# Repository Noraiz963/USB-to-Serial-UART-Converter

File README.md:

# USB to Serial (UART) Converter

A USB Type-C to Serial (UART) converter designed in KiCad, built around the CP2102 USB-to-UART bridge IC — lets you connect a microcontroller's serial pins to a computer's USB port for programming, debugging, or serial communication.

## Why This Exists

Modern PCs only expose USB — there's no native way to talk to a device that "speaks" UART (TX/RX serial). The CP2102 sits in between and acts as a protocol translator: it handles USB enumeration and packetization on one side, and generates real asynchronous serial (UART) signals on the other. Once connected, the PC's OS loads it as a **Virtual COM Port** (e.g. `COM5` on Windows, `/dev/ttyUSB0` on Linux), so any serial terminal or IDE (Arduino Serial Monitor, PuTTY, minicom) can talk to the target microcontroller exactly as if it were plugged into a physical RS-232 port.

## Circuit Overview

- **USB Type-C input**: USB-C receptacle (J1) with CC1/CC2 pull-down resistors for proper USB-C power delivery negotiation, plus ESD protection
- **USB-to-UART bridge**: CP2102 (U1) handles the USB-to-serial conversion, exposing TX/RX lines on the output header
- **Status indicator**: LED with current-limiting resistor, indicating activity/power
- **Decoupling**: Capacitors placed across VBUS/VDD to stabilize the CP2102's supply
- **Reset**: RST line broken out to the output header for manual reset control
- **Output header**: 5-pin header exposing RST, TX, RX, VBUS, and GND — standard pinout for connecting to microcontroller boards (e.g. ESP32, STM32, Arduino) for flashing or serial monitoring

## Signal Flow (Concept)

**PC → Target device (TX path):**
1. PC sends data over USB D+/D− as standard USB packets.
2. CP2102's internal USB engine strips the packet down to raw bytes.
3. CP2102 serializes each byte into UART bits (start bit, 8 data bits, stop bit) at the configured baud rate.
4. Output appears on the CP2102's **TX pin**, routed to J2, then into the target device's **RX pin**.

**Target device → PC (RX path):**
1. Target device sends serial data out its **TX pin** into the CP2102's **RX pin** (via J2).
2. CP2102 samples the incoming UART bitstream and reconstructs it into bytes.
3. Those bytes are packaged into USB packets by the CP2102's internal USB controller.
4. Packets are sent back to the PC over D+/D−, where the VCP driver hands them to whatever serial application is listening.

**Power path:**
- USB-C VBUS (5V) enters through J1 → CC resistors confirm valid power negotiation → CP2102's internal LDO regulates it to 3.3V for internal logic → VBUS is also broken out on J2 to optionally power the target board directly from USB.

**Ground referencing:**
- GND is shared across the USB connector, the CP2102, and the output header. This is critical — UART logic levels (HIGH/LOW) are only meaningful relative to a common ground; without it, the target device can't correctly interpret the TX/RX voltage transitions.

**Reset behavior:**
- RST is pulled high by default (idle/running state) via a pull-up resistor. Pulling it low resets the CP2102. Broken out to J2 so it can optionally be wired to a target MCU's reset line for auto-reset-on-connect behavior (common on Arduino-style boards).

## Schematic

## PCB Layout

## 3D Render

## Bill of Materials

| Ref | Component | Value |
|-----|-----------|-------|
| J1 | USB Type-C Receptacle | — |
| U1 | USB-to-UART Bridge IC | CP2102 |
| D1, D2 | LED / Protection Diode | — |
| R1–R7 | Resistor | Various (pull-downs, current limiting) |
| C1, C3, C4, C10, C11 | Capacitor | Decoupling |
| J2 | Header (5-pin) | RST / TX / RX / VBUS / GND |

## Output Header Pinout (J2)

| Pin | Signal | Direction (from board) | Notes |
|-----|--------|-------------------------|-------|
| 1 | RST | — | Optional reset control for target MCU |
| 2 | TX | Out | Connect to target device's RX |
| 3 | RX | In | Connect to target device's TX |
| 4 | VBUS | Out | 5V from USB, optional power for target |
| 5 | GND | — | Common ground reference |

> ⚠️ Always cross-connect TX ↔ RX between this board and the target device — never TX to TX.

## Tools Used
- KiCad 10.0 (schematic capture, PCB layout, 3D visualization)

## Status
Completed — fifth PCB design project, first design centered on a USB interface IC rather than power regulation or timer-based circuits.

## Notes
Built as a learning project to understand USB-C connector wiring (CC resistor requirements) and USB-to-serial bridge IC integration — a practical, reusable tool for future embedded projects that need programming/debugging headers.

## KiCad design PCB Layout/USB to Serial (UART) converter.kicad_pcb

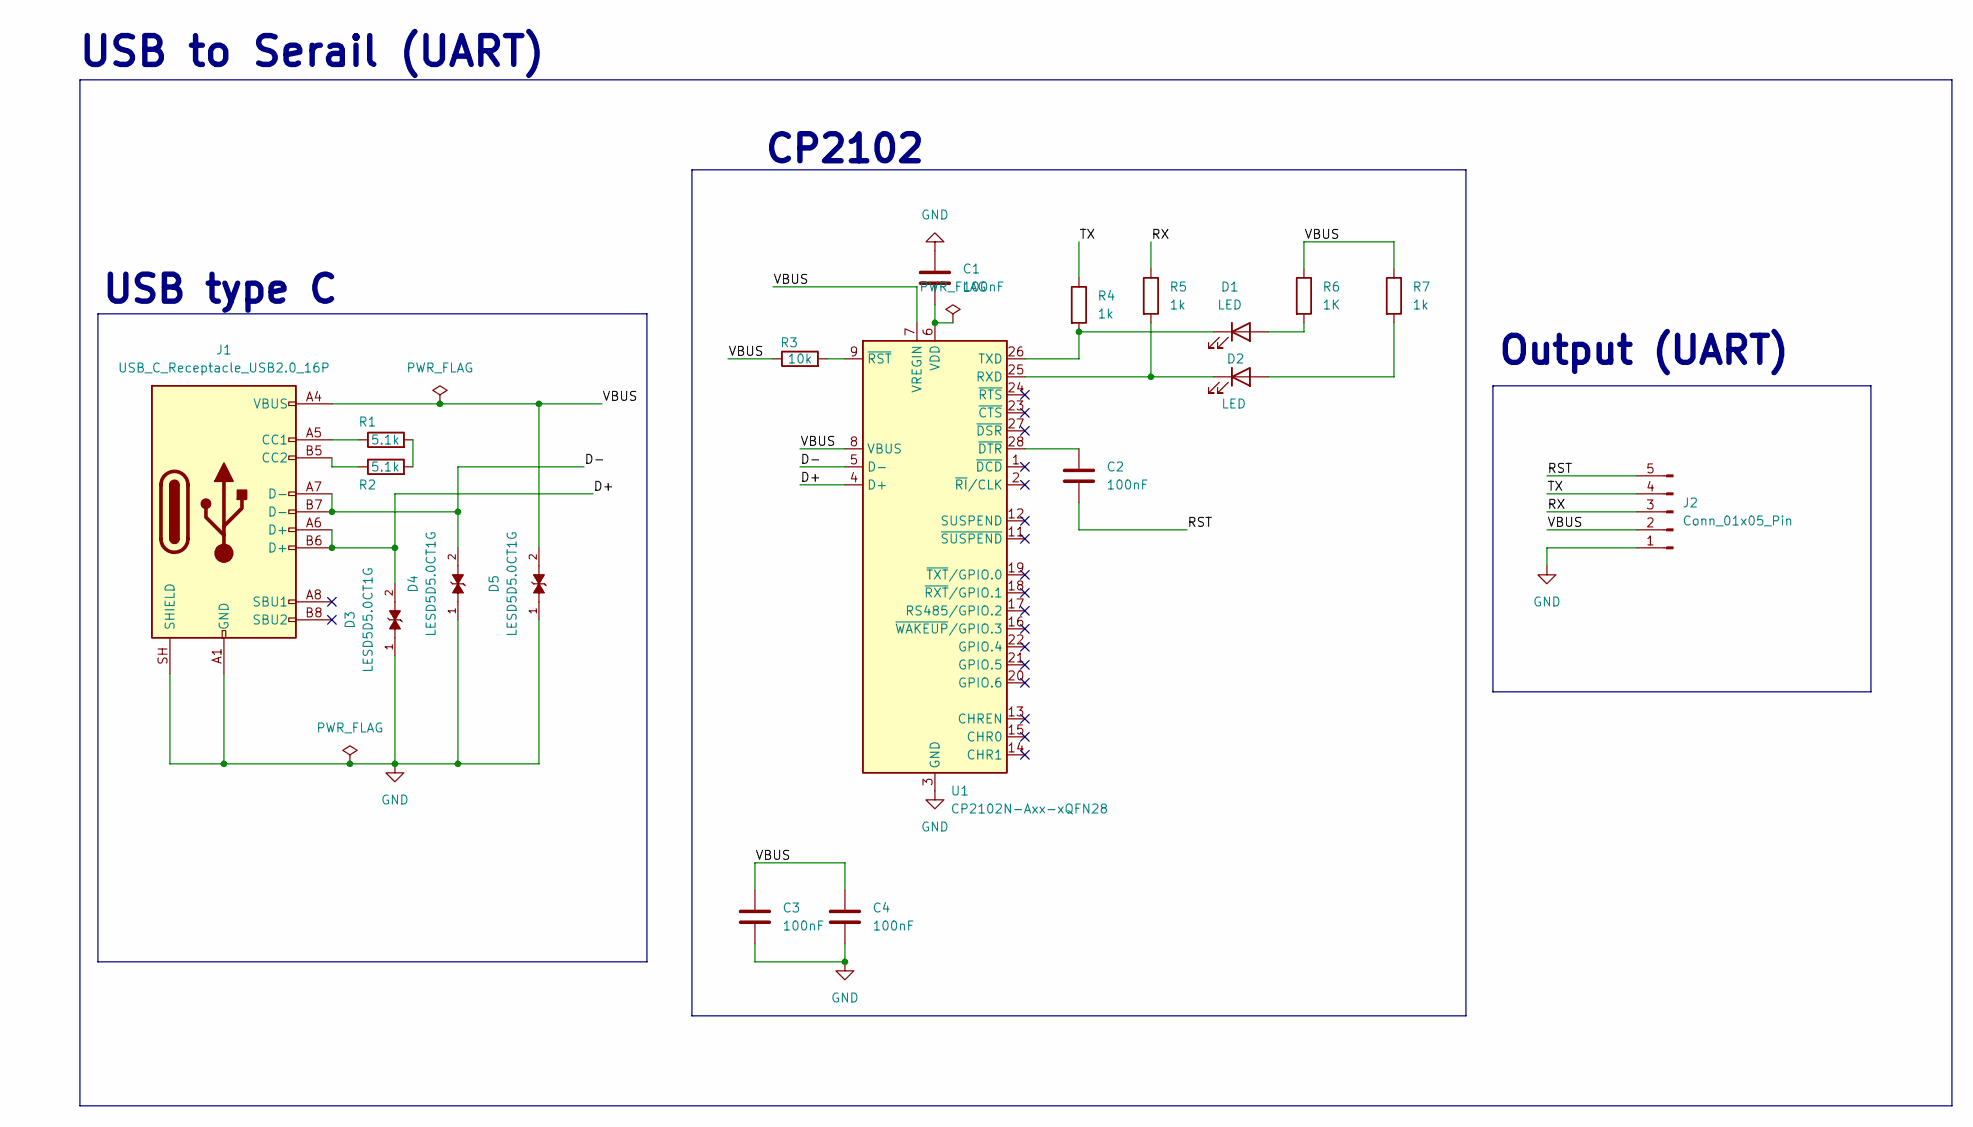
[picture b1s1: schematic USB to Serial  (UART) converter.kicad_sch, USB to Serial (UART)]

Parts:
C1, C2, C3, C4: 100nF; C_0201_0603Metric
D1, D2: LED; LED_0201_0603Metric
D3, D4, D5: LESD5D5.0CT1G; TVS_LESD5D5.0CT1G; PARTREV O
J1: USB_C_Receptacle_USB2.0_16P; USB_C_Receptacle_HRO_TYPE-C-31-M-12
J2: Conn_01x05_Pin; PinHeader_1x05_P2.54mm_Horizontal
R1, R2: 5.1k; R_0201_0603Metric
R3: 10k; R_0201_0603Metric
R4, R5, R7: 1k; R_0201_0603Metric
R6: 1K; R_0201_0603Metric
U1: CP2102N-Axx-xQFN28; QFN-28-1EP_5x5mm_P0.5mm_EP3.35x3.35mm

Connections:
/D+: D3.2, J1.A6 (D+), J1.B6 (D+), U1.4 (D+)
/D-: D4.2, J1.A7 (D-), J1.B7 (D-), U1.5 (D-)
/RST: C2.2, J2.5
/RX: J2.3, R5.1
/TX: J2.4, R4.1
/VBUS: C3.1, C4.1, D5.2, J1.A4 (VBUS), J1.A9 (VBUS), J1.B4 (VBUS), J1.B9 (VBUS), J2.2, R3.1, R6.1, R7.1, U1.7 (VREGIN), U1.8 (VBUS)
GND: C1.1, C3.2, C4.2, D3.1, D4.1, D5.1, J1.A1 (GND), J1.A12 (GND), J1.B1 (GND), J1.B12 (GND), J1.SH (SHIELD), J2.1, U1.3 (GND), U1.29 (GND)
unnamed: D1.2 (A), R6.2
unnamed: D1.1 (K), R4.2, U1.26 (TXD)
unnamed: D2.2 (A), R7.2
unnamed: D2.1 (K), R5.2, U1.25 (RXD)
unnamed: J1.A5 (CC1), R1.1
unnamed: J1.B5 (CC2), R2.1
unnamed: R1.2, R2.2
unnamed: C1.2, U1.6 (VDD)
unnamed: C2.1, U1.28 (~DTR)
unnamed: R3.2, U1.9 (~RST)

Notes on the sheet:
CP2102
Output (UART)
USB type C
USB to Serail (UART)

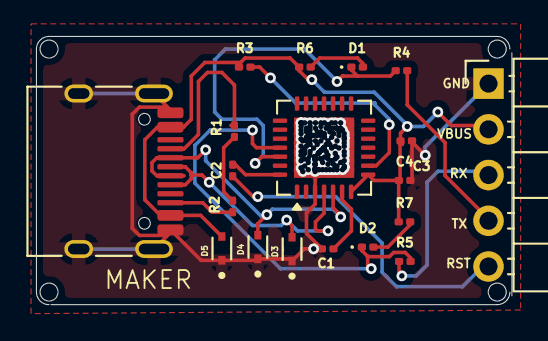
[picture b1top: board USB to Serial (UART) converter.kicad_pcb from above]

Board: 2 copper layers, 26.4 x 14.9 mm, 19 parts (0 on the bottom side), 17 nets.
